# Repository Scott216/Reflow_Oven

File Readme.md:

Reflow Oven Controller <br>

I found a nice toaster oven when I when I was dropping some garbage off at our town's e-waste dumpster.  It was in excellent condition.  It has heating three heating elements on the top and three on the bottom . It had a microcontroller to control everything, so it was a bit more complex then a toaster with just a couple of knobs.  My plan was to remove the micro controller PCB and replace it with my own.  The heating elements are controlled by a couple of (triacs BTA26-600B).  I hadn't used triacs before and had to do a little research on them.  One unusual aspect of the toaster design is that the microcontroller board was floating on the 110 VAC line.  This means that the 5 VDC supply voltage was over 100 volts if measure from mains ground.  But the digital ground was only 5 volts less.  So to the micro controller board this was fine, but the whole PCB was essentially about 110 VAC.  I wasn't really comfortable with this, so I hacked the power supply board a bit so it output straight 5 volts.  it also output -9 volts. <br>

I wanted to continue to use the big start button from the front panel, so I took the original micro controller PCB and cut it in half to keep the start button and the LEDs that lit it up.  Then I soldered some wires in a header that connected to the button and LEDs.<br>

I designed a PCB with Cadsoft Eagle and milled it out on my [ShapeOko](http://www.shapeoko.com/) CNC router.  This was one of the first PCBs I did on the ShapeOko and it turned out pretty well (after a few revs). 
I had to figure out how to trigger the triacs properly.  At first I didn't realize I had to trigger when the AC voltage crossed zero volts, this cause some magic smoke to be released from one of the resistors.  This was easily fixed.  Then I got a couple of Fairchild [MOC3032](http://www.digikey.com/product-search/en?keywords=MOC3032M-ND) zero-crossover opto-couplers.  I had a Nokia 5110 display from Adafruit which was a great fit for the existing display window.  I used an Arduino [Pro-mini](http://www.sparkfun.com/products/11114) (3.3 v) from Sparkfun to control everything.  To measure the temperature I have a [thermocouple](http://www.adafruit.com/products/270) from Adafruit and Adafruit's [thermocouple amplifier](http://www.adafruit.com/products/269).  <br>

For the Arduino code I started with code from here: http://github.com/CvW/Reflow-Oven-Controller/, which is based on code from [Rocketscream](http://github.com/rocketscream/Reflow-Oven-Controller).  There was a bug in the debounce code I fixed and I replaced the MAX6675 with MAX31855 thermocouple amplifier.   There a bunch of other little changes, nothing major.  The code has two solder temperature profiles that you can choose between (by pressing the bake button) - one for leaded paste and one for a low-temp paste <br>

This toaster is not a convection toaster where it circulates the air around, but I thought this would be a nice feature. So I used a little motor that I salvaged from an inkjet printer to power a 3.5 inch aluminum fan blade I ordered from McMaster (17545K63).  I used a 3/16 bronze flange busing (McMaster 9440T63) to support the brass shaft through the sheet metal side. The fan is a bit noisy, but works pretty well.  Since the reflow oven isn't an that long, not a lot of heat is conducted to the motor from the shaft. <br>  

I would like to have an interior light to illuminate the PCB as it's being reflowed, but I haven't figured out how to do that yet. <br>

You can see some pictures on [flickr](https://www.flickr.com/photos/37101040@N00/sets/72157645550432296/) or in the \photos directory of the repo. <br>

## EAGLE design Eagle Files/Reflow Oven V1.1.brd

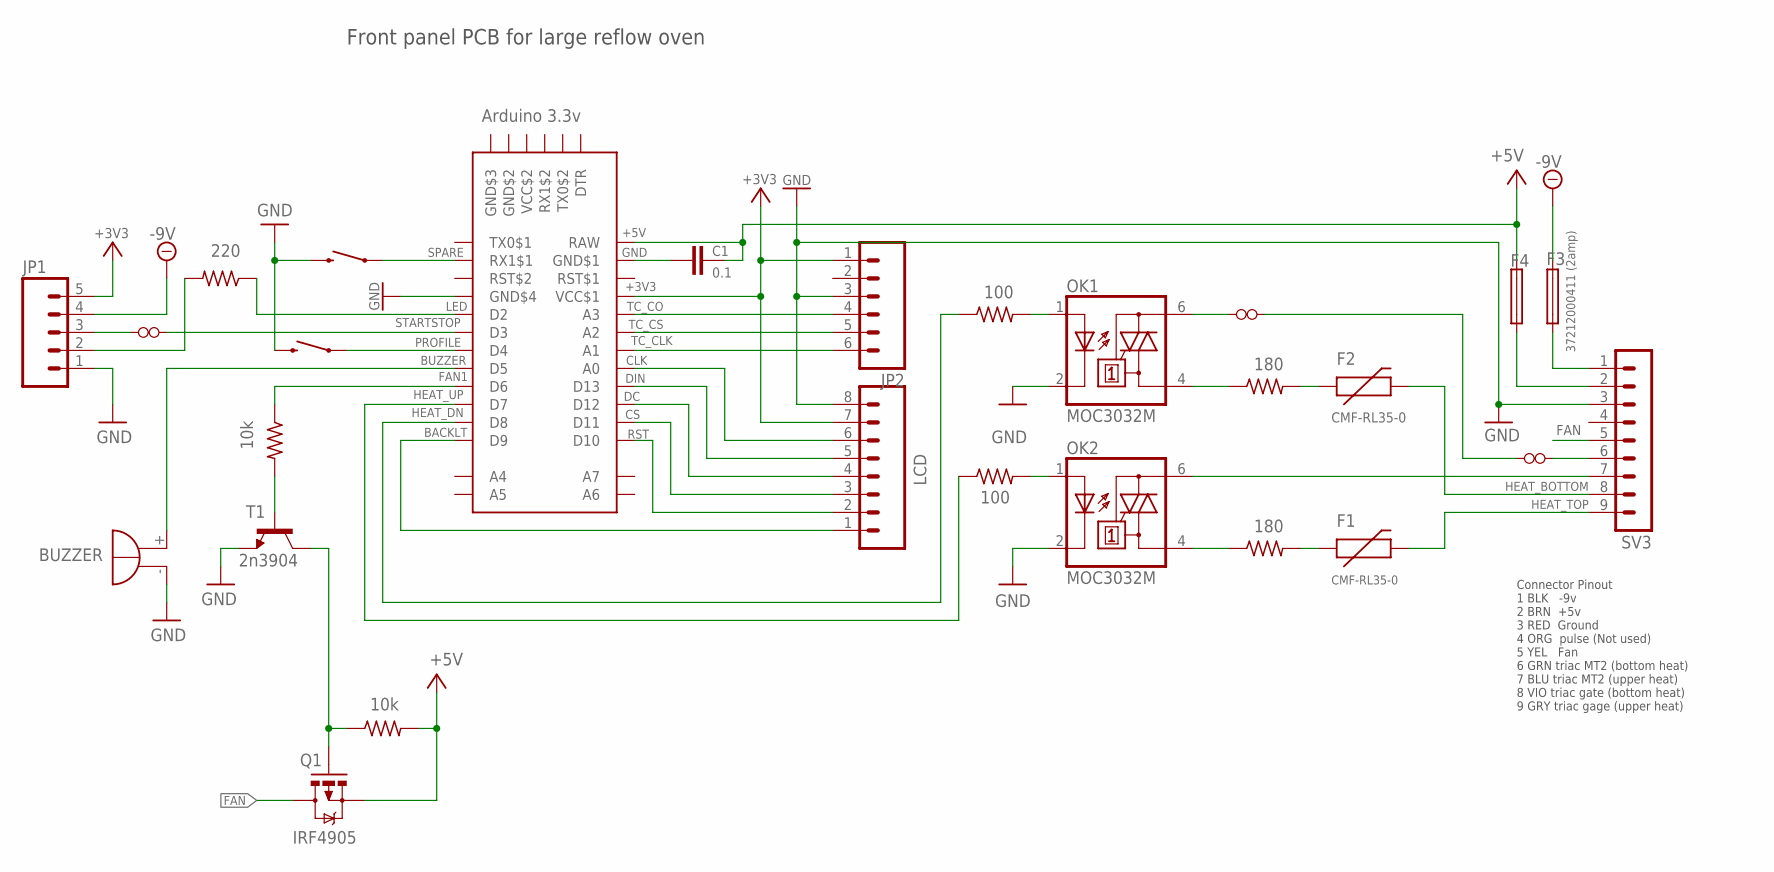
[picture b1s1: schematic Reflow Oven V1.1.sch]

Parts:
BUZZER: F/HMB
C1: 0.1; CAP-PTH-SMALL
F1, F2: CMF-RL35-0; PTC
F3, F4: 37212000411 (2amp); 19560
JP1: M05PTH; 1X05
JP2: M06SIP; 1X06
LCD: M081X08; 1X08
OK1, OK2: MOC3032M; DIL06
PROFILE: SWITCH-MOMENTARY-2PTH; TACTILE-PTH
Q1: IRF4905; TO220V
R2, R5: 100; 0207/10
R3, R4: 180; 0207/12
R11, R13: 10k; 0207/10
R12: 220; 0207/10
SPARE: SWITCH-MOMENTARY-2PTH; TACTILE-PTH
SV3: MA09-1
T1: 2n3904; TO92-EBC
U$1, U$4: JUMPER0.3_INCH; JUMPER_0.3
U$2: Arduino 3.3v; ARDUINO_PRO_MINI
U$5: JUMPER0.7INCH; JUMPER_0.7

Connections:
+3V3: JP1.5, JP2.1, LCD.7, U$2.VCC$1
+5V: C1.1, F4.2, Q1.3 (S), R13.2, U$2.RAW
-9V: F3.2, JP1.4
BACKLT: LCD.1, U$2.D9
BUZZER: BUZZER.+, U$2.D5
CLK: LCD.6, U$2.A0
CS: LCD.3, U$2.D11
DC: LCD.4, U$2.D12
DIN: LCD.5, U$2.D13
FAN: Q1.2 (D), SV3.5
FAN1: R11.1, U$2.D6
F_GATE: Q1.1 (G), R13.1, T1.C
GND: BUZZER.-, JP1.1, JP2.3, LCD.8, OK1.2 (C), OK2.2 (C), PROFILE.3 (2), SPARE.3 (2), SV3.3, T1.E, U$2.GND$4
GND2: C1.2, U$2.GDN$1 (GND$1)
GND$2: U$2.GND$2
GND$3: U$2.GND$3
HEAT_BOTTOM: F2.P$2 (2), SV3.8
HEAT_DN: R5.1, U$2.D8
HEAT_TOP: F1.P$2 (2), SV3.9
HEAT_UP: R2.1, U$2.D7
LED: R12.1, U$2.D2
unnamed: OK1.4 (A1), R3.1
unnamed: OK2.6 (A2), SV3.7
unnamed: F2.P$1 (1), R3.2
unnamed: F4.1, SV3.2
unnamed: F1.P$1 (1), R4.2
unnamed: OK2.4 (A1), R4.1
unnamed: U$1.P$1, U$5.P$2
unnamed: SV3.6, U$1.P$2
unnamed: OK1.1 (A), R5.2
unnamed: OK1.6 (A2), U$5.P$1
unnamed: OK2.1 (A), R2.2
unnamed: JP1.3, U$4.P$1
unnamed: F3.1, SV3.1
unnamed: R11.2, T1.B
unnamed: JP1.2, R12.2
PROFILE: PROFILE.1, U$2.D4
RST: LCD.2, U$2.D10
SPARE: SPARE.1, U$2.RX1$1
STARTSTOP: U$2.D3, U$4.P$2
TC_CLK: JP2.6, U$2.A1
TC_CO: JP2.4, U$2.A3
TC_CS: JP2.5, U$2.A2
VCC$2: U$2.VCC$2

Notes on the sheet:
Front panel PCB for large reflow oven
Connector Pinout 1 BLK -9v 2 BRN +5v 3 RED Ground 4 ORG pulse (Not used) 5 YEL Fan 6 GRN triac MT2 (bottom heat) 7 BLU triac MT2 (upper heat) 8 VIO triac gate (bottom heat) 9 GRY triac gage (upper heat)

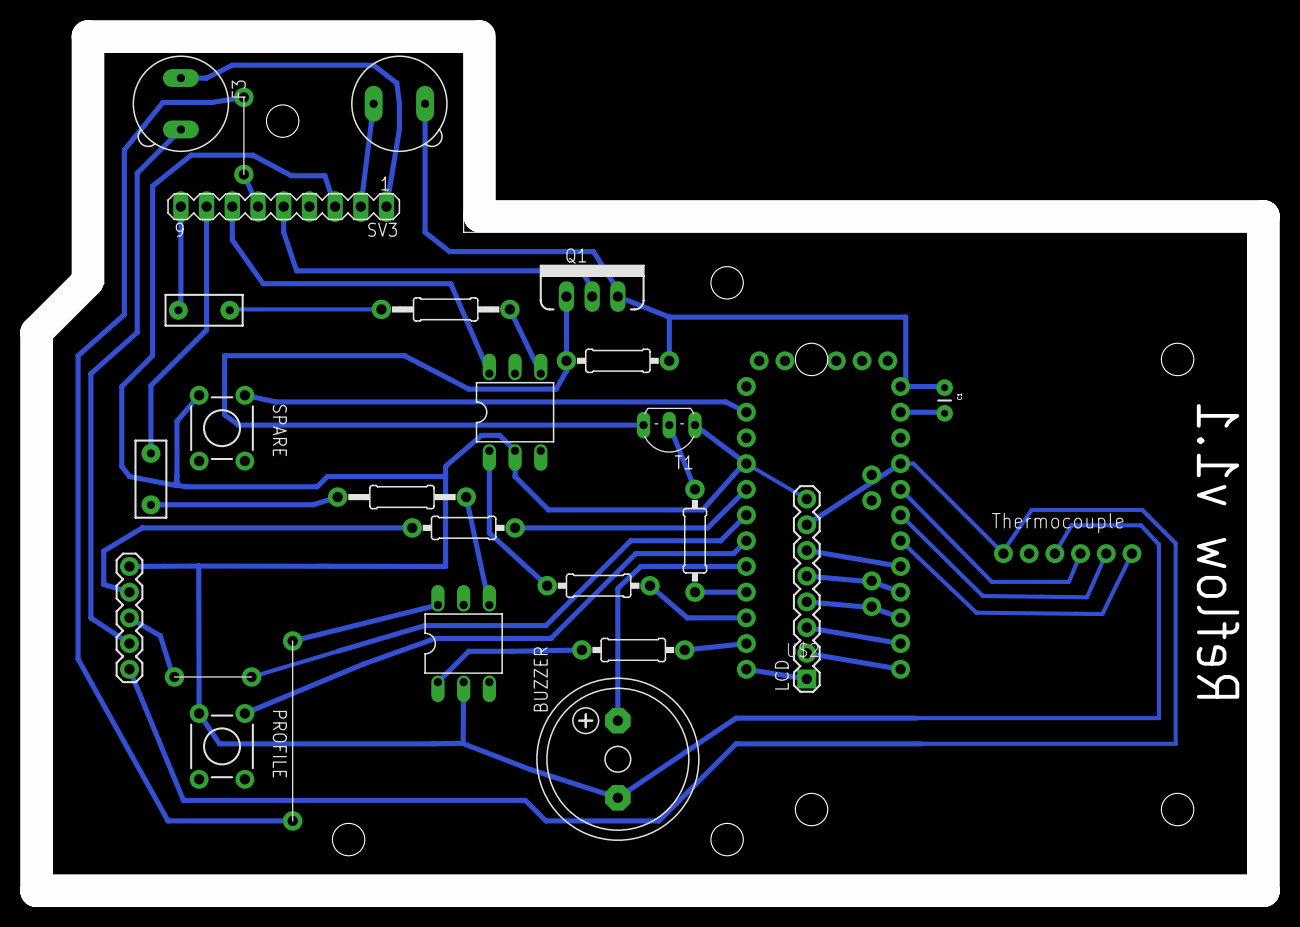
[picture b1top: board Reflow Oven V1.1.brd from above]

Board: 2 copper layers, 121.3 x 84.5 mm, 27 parts (1 on the bottom side), 41 nets.

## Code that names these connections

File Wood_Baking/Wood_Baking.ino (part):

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const int thermocoupleCLK = A1;

// I/O
const int spareBtn =          1;  // Spare pushbutton
const int changeProfileBtn  = 4;  // Change profile button, , on interrupt pin (in case you want to use them
const int cycleStartStopBtn = 3;  // Start-stop button, on interrupt pin (in case you want to use them
const int grnLED =            2;  // Blinks when oven is on
const int buzzer =            5;  // PWM pin - useful if you want to use a piezo buzzer
const int fan =               6;  // PWM pin
const int heater_top =        7;
const int heater_bottom =     8;

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  pinMode(dispLED,                 OUTPUT);  // pwm output
  pinMode(heater_top,              OUTPUT);
  pinMode(heater_bottom,           OUTPUT);
  pinMode(fan,                     OUTPUT);  // pwm output
  pinMode(buzzer,                  OUTPUT);
  pinMode(grnLED,                  OUTPUT);
  pinMode(cycleStartStopBtn, INPUT_PULLUP);
  pinMode(changeProfileBtn,  INPUT_PULLUP);
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
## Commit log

2014-03-07 Based on RocketScream version
    Based on Rocketscream’s version. Removed MAX6675 and used Adafruit’s
    MAX31855 library.
2014-03-07 Switched to CvW version
    Rev 1.21. Changed to CvW version which has two profiles. Replaced
    MAX6675 with MAX31855
2014-03-07 Switched to CvW version
2014-03-09 Changed LCD, profile temps, t/c errors
    v 1.22 - Moved LCD display code to separate function, added NAN error
    checking on thermocouple, changed profiles to leaded and low temp,
    changed LED output so HIGH is on
2014-03-11 v1.23 - fixed button errors, changed I2C lib, moved inputs
    Took typedef out of enum, moved buttons to D0 & D1 because of I2C
    conflict, changed I2C library, removed debounce for button #2, it was
    causing wrong code to run
2014-03-12 v1.24 minor changes
    Updated profile temperatures, moved some code out of loop() into
    functions, removed 2 line LCD code. Added seconds and rate to LCD
    display. Changed some variables
2014-03-12 Changed URLs
2014-03-12 Low Temp Solder Data Sheet
2014-03-13 v1.25 setup for Pro-Mini
    Change pins for Mini-Pro, changed C/Sec to average over 5 seconds
2014-04-16 Committed ver 1.29
2014-04-16 Heat profile data
2014-04-25 added micro stepping for pre-heat
    Also worked on buzzer so it beeps after each stage.
2014-06-26 Photos
2014-06-26 Swapped D2 & D4, adjusted contrast
2014-06-26 Eagle Files
2014-06-26 Added build info
2014-06-26 Added links
2014-07-10 Added flickr link
2015-01-04 v1.35 changed contrast
2015-09-02 v1.36 formatting, changed contrast
2015-09-02 v1.37 - Added limit to temp setpoint
    Limited setpoint temp and renamed a few global variables

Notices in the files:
parts and their libraries:
SparkFun-PowerIC: Licensing: CC v3.0 Share-Alike You are welcome to use this library for commercial purposes.
SparkFun-DiscreteSemi: Licensing: Creative Commons ShareAlike 4.0 International - https://creativecommons.org/licenses/by-sa/4.0
